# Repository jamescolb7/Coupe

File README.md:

# Coupé

A modern Bluetooth audio system for your vehicle.

## What is it?

The Coupé is a small ESP32 powered drop-in infotainment system for your vehicle. It receives audio over Bluetooth from your mobile device and plays it to your car through an I2S compatible DAC. It also consists of a 3.2 inch touch display that indicates what song is playing, artist, album, along with the cover art.

## Building

These are the steps for building your own Coupé.

### Parts List

Below is a general parts list of what you may need. If you choose to build one without a PCB, you may need wire and a breadboard/perfboard. If you choose to use a PCB, you may want to ensure you have a soldering iron and solder. You may also want to have a 3D printer on hand (the 3D print shown here has been printed on both the Bambu X1E and P2S).

| Part | Role | Description | Vendor |
| --- | --- | --- | --- |
| ESP32 WROVER | MCU | Selected due to built in 4-8 MB of PSRAM, Classic BT | AliExpress
| PCM5102a | DAC | Excellent sound quality and reasonable signal strength w/o amplification | AliExpress
| Generic ILI9341/XPT2046 3.2" TFT Touch Display | Display | Reasonably cost effective, decently large, touch, typically with a red PCB | AliExpress
| Custom PCB (Optional) | PCB | KiCad PCB design provided | JLCPCB (or other)
| 3D Printed Enclosure (Optional) | Case | Fusion 360 .f3d and .3mf provided | PLA/PETG

### Schematic
As a general guide to how everything is going to be connected, below is the schematic. Here, the USB C receptacle is fully optional, as it is only supplying 5V to the AMS1117 on the ESP32 board itself, which could be done with its own UART connector regardless. Making all connections listed in this schematic will allow you to have a working prototype before ordering a custom PCB.

### PCB
Below is the PCB that will be used for the project. Its dimensions are 90 mm x 56 mm, being just larger than the 3.2" display. It is shown below:

Currently, my PCB fab of choice is JLCPCB, as they have been easiest to work with so far. The KiCad project included is also already set for their machine tolerances and has been confirmed to work.

To order a PCB, you will have to manually generate Gerbers and drilling files. A good guide from JLC to do this can be found here:

https://jlcpcb.com/help/article/how-to-generate-gerber-and-drill-files-in-kicad-9

Currently, this board is set up to be 4 layers, however it could be reduced to 2 by removing the two inner layers.

### 3D Printed Enclosure

Readme to be completed...

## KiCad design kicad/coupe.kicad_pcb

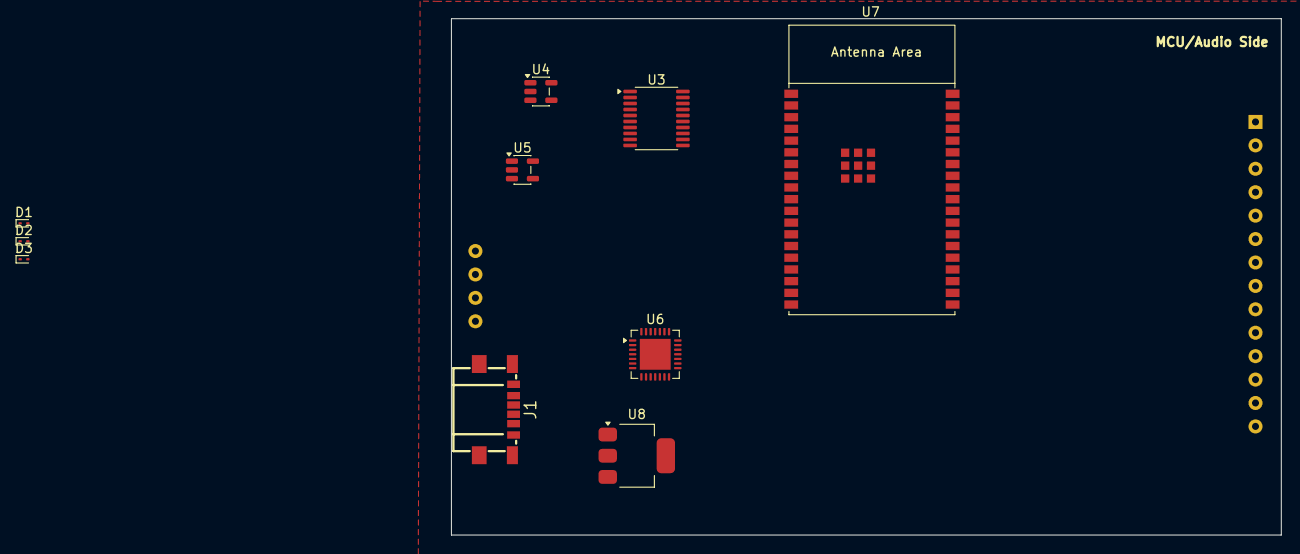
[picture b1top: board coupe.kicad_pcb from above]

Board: 4 copper layers, 90.0 x 56.0 mm, 11 parts (1 on the bottom side), 18 nets, no tracks yet.

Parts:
D1, D2, D3: ESD9B5.0ST5G; D_SOD-923
J1: USB_C_Receptacle_PowerOnly_6P; USB-C-SMD_TYPE-602-T3
U2: ILI9341 + XPT2046
U3: PCM5102A; TSSOP-20_4.4x6.5mm_P0.65mm
U4, U5: ME6211C33M5; SOT-23-5
U6: CP2102N-Axx-xQFN28; QFN-28-1EP_5x5mm_P0.5mm_EP3.35x3.35mm
U7: ESP32-WROVER-E
U8: AMS1117-3.3; SOT-223-3_TabPin2

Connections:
+3.3V: U2.1 (VCC), U7.2 (3V3), U8.2 (VO)
+5V: D3.2 (A2), U4.1 (V_{IN}), U4.3 (CE), U5.1 (V_{IN}), U5.3 (CE), U6.7 (VREGIN), U8.3 (VI)
DISP_CS: U2.3 (CS), U7.23 (MTDO/GPIO15/ADC2_CH3)
DISP_DC: U2.5 (DC), U7.24 (ADC2_CH2/GPIO2)
DISP_RST: U2.4 (RESET), U7.26 (ADC2_CH0/GPIO4)
GND: D1.1 (A1), D2.1 (A1), J1.A12 (GND), J1.B12 (GND), J1.SH (SHIELD), U2.2 (GND), U3.10 (DEMP), U3.11 (FLT), U3.16 (FMT), U6.3 (GND), U6.29 (GND), U7.1 (GND), U7.15 (GND), U7.38 (GND), U8.1 (GND)
unnamed: D1.2 (A2), J1.B5 (CC2), U6.4 (D+)
unnamed: D2.2 (A2), J1.A5 (CC1), U6.5 (D-)
unnamed: D3.1 (A1), J1.A9 (VBUS), J1.B9 (VBUS)
unnamed: U3.1 (CPVDD), U3.8 (AVDD), U4.5 (V_{OUT})
unnamed: U3.17 (XSMT), U3.20 (DVDD), U5.5 (V_{OUT})
SD_CS: U2.15 (SD_CS), U7.13 (MTMS/GPIO14/ADC2_CH6)
SPI_LED: U2.8 (LED), U7.36 (GPIO22)
SPI_MOSI: U2.6 (SDI(MOSI)), U2.12 (T_DIN), U2.16 (SD_MOSI), U7.37 (GPIO23)
SPI_SCK: U2.7 (SCK), U2.10 (T_CLK), U2.18 (SD_SCK), U7.30 (GPIO18)
SPI_SDO: U2.9 (SDO(MISO)), U2.13 (T_DO), U2.17 (SD_MISO), U7.31 (GPIO19)
TOUC_CS: U2.11 (T_CS), U7.8 (32K_XP/GPIO32/ADC1_CH4)
TOUC_IRQ: U2.14 (T_IRQ), U7.9 (32K_XN/GPIO33/ADC1_CH5)
